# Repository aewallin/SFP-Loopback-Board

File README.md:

# SFP-Loopback-Board
SFP optical transciever loopback board. Connects SFP TX pins to RX pins, and provides buffered ( [ONET1191](http://www.ti.com/product/ONET1191P) )probe-outputs on SMA connectors.

See also [SFP+ timing calibration module](https://ohwr.org/project/wr-calibration/wikis/Electrical-absolute-calibration)

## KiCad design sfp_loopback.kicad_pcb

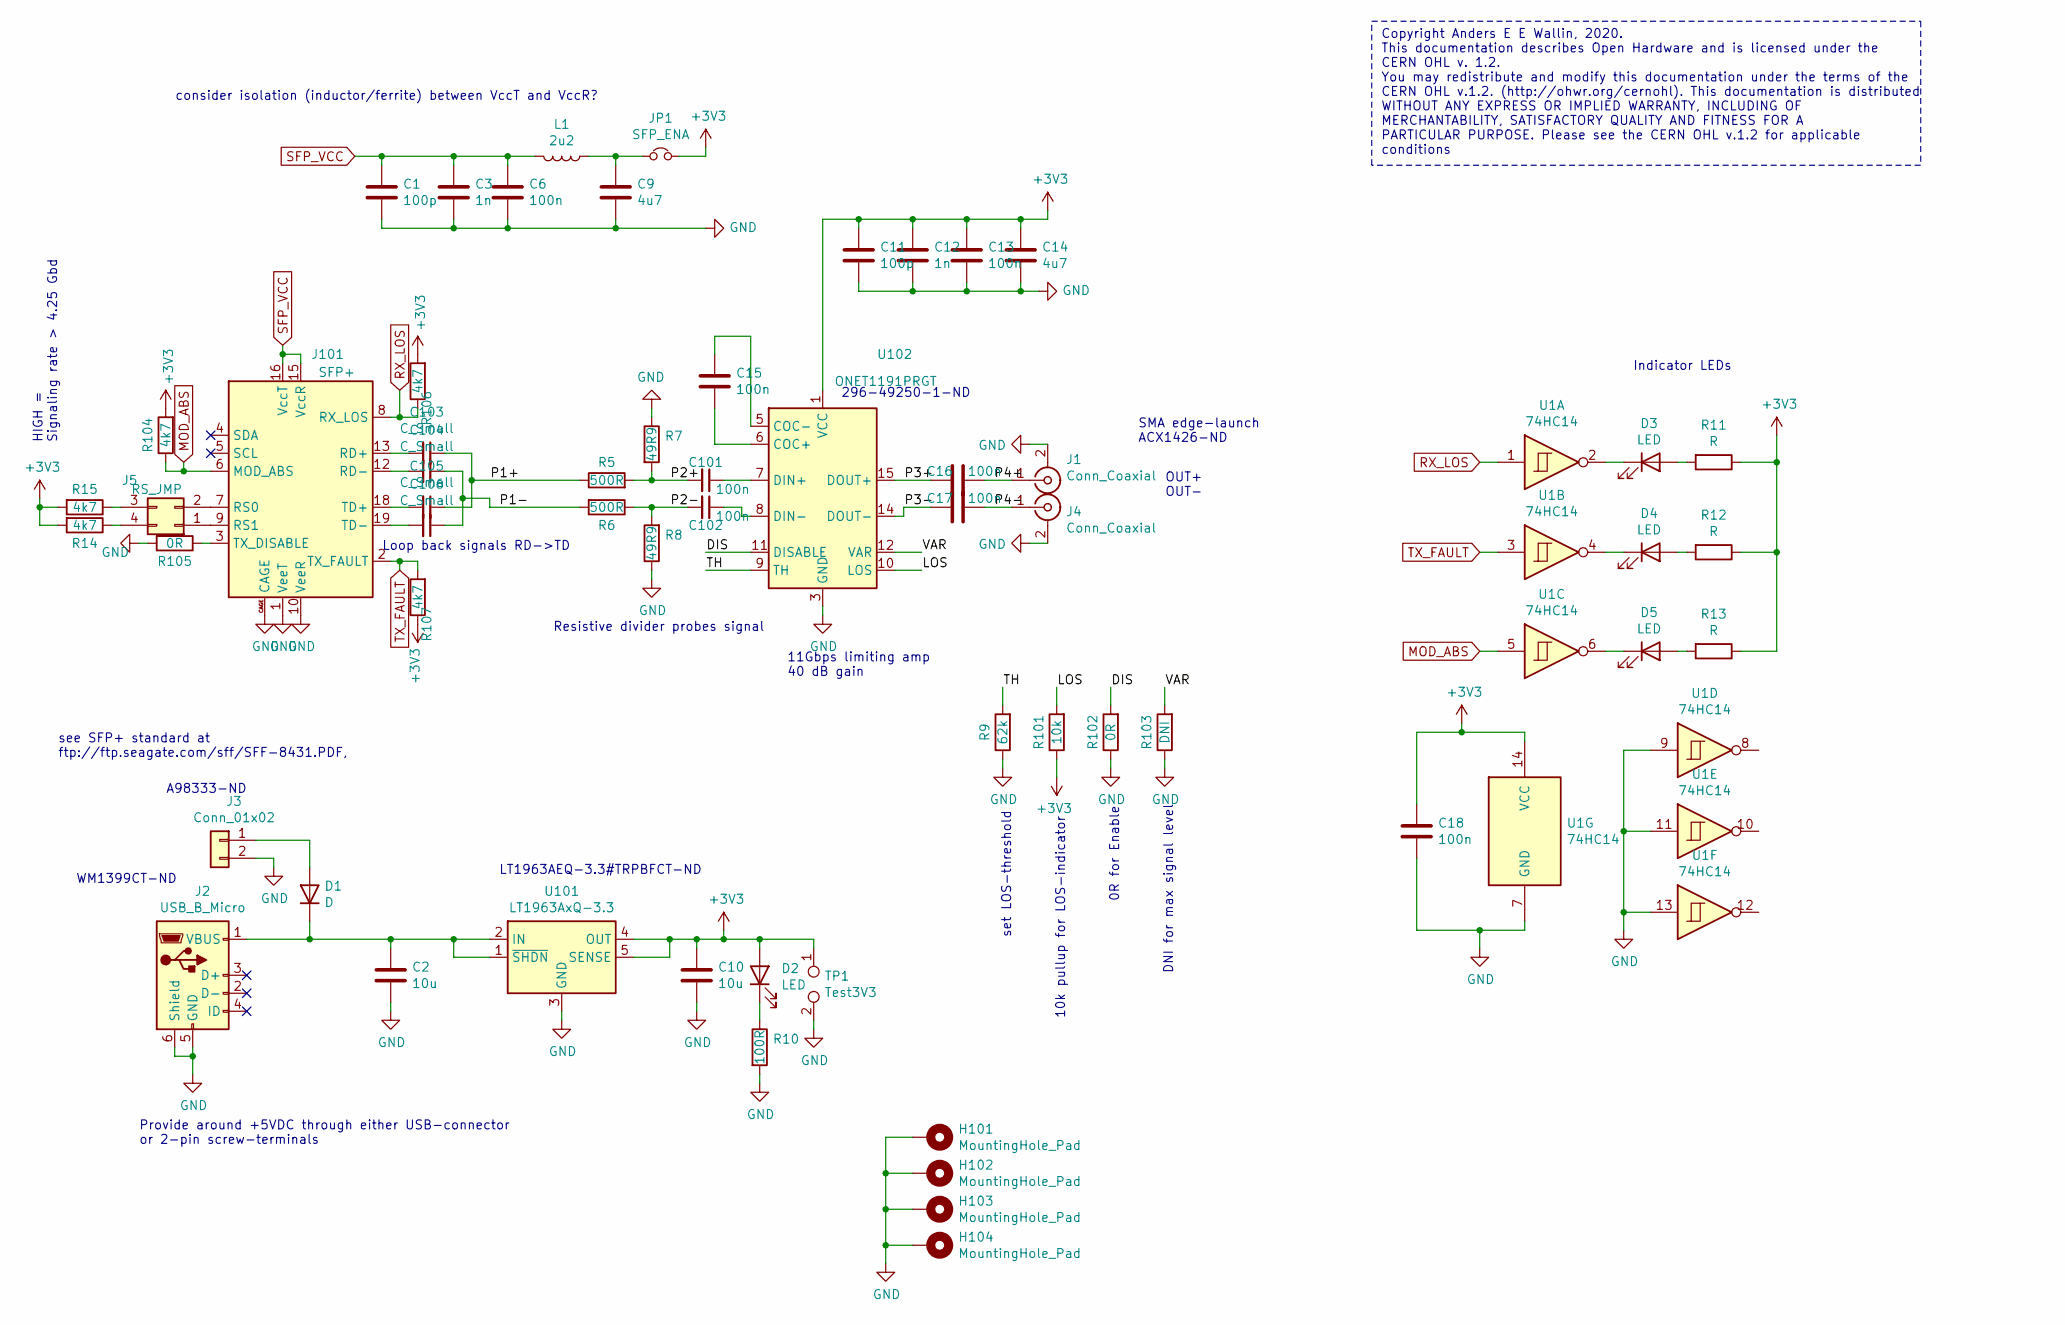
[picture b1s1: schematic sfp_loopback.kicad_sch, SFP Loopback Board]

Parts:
C1: 100p; C_0603
C2, C10: 10u; C_0805
C3, C12: 1n; C_0805
C6, C13, C16, C17, C18: 100n; C_0805
C9, C14: 4u7; C_0805
C11: 100p; C_0805
C15: 100n; C_0402
C101, C102: 100n; C_0402_1005Metric
C103, C104, C105, C106: C_Small; C_0402_1005Metric
D1: D; D_1206_3216Metric
D2, D3, D4, D5: LED; LED_0805
H101, H102, H103, H104: MountingHole_Pad; MountingHole_3.2mm_M3_DIN965_Pad
J1, J4: Conn_Coaxial; SMA_Amphenol_132289_EdgeMount
J2: USB_B_Micro; USB_Micro-B_Molex-105017-0001
J3: Conn_01x02; Pin_Header_Straight_1x02_Pitch2.54mm
J5: RS_JMP; Pin_Header_Straight_2x02_Pitch2.54mm
J101: SFP+; Connector_SFP_and_Cage
JP1: SFP_ENA; Pin_Header_Straight_1x02_Pitch2.54mm
L1: 2u2; L_0805
R5, R6: 500R; R_0402
R7, R8: 49R9; R_0402
R9: 62k; R_0805_2012Metric
R10: 100R; R_0805_2012Metric
R11, R12, R13: R; R_0805
R14, R15, R104, R106, R107: 4k7; R_0805_2012Metric
R101: 10k; R_0805_2012Metric
R102, R105: 0R; R_0805_2012Metric
R103: DNI; R_0805_2012Metric
TP1: Test3V3; Pin_Header_Straight_1x02_Pitch2.54mm
U1: 74HC14; TSSOP-14_4.4x5mm_Pitch0.65mm
U101: LT1963AxQ-3.3; TO-263-5_TabPin3
U102: ONET1191PRGT; VQFN-16-1EP_3x3mm_P0.5mm_EP1.68x1.68mm

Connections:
+3V3: C10.1, C11.2, C12.2, C13.2, C14.2, C18.1, D2.2 (A), JP1.2, R11.1, R12.1, R13.1, R14.2, R15.2, R101.1, R104.2, R106.2, R107.1, TP1.1, U1.14 (VCC), U101.4 (OUT), U101.5 (SENSE), U102.1 (VCC), U102.2 (VCC)
/DIS: R102.2, U102.11 (DISABLE)
/LOS: R101.2, U102.10 (LOS)
/P1+: C103.1, C105.1, R5.1
/P1-: C104.1, C106.1, R6.2
/P2+: C101.2, R5.2, R7.2
/P2-: C102.2, R6.1, R8.2
/P3+: C16.2, U102.15 (DOUT+)
/P3-: C17.2, U102.14 (DOUT-)
/P4+: C16.1, J1.1 (In)
/P4-: C17.1, J4.1 (In)
/TH: R9.2, U102.9 (TH)
/VAR: R103.2, U102.12 (VAR)
GND: C1.1, C2.2, C3.1, C6.1, C9.1, C10.2, C11.1, C12.1, C13.1, C14.1, C18.2, H101.1, H102.1, H103.1, H104.1, J1.2 (Ext), J2.5 (GND), J2.6 (Shield), J3.2, J4.2 (Ext), J101.1 (VeeT), J101.10 (VeeR), J101.11 (VeeR), J101.14 (VeeR), J101.17 (VeeT), J101.20 (VeeT), J101.CAGE, R7.1, R8.1, R9.1, R10.2, R102.1, R103.1, R105.2, TP1.2, U1.7 (GND), U1.9, U1.11, U1.13, U101.3 (GND), U102.3 (GND), U102.4 (GND), U102.13 (GND), U102.16 (GND), U102.17 (GND)
MOD_ABS: J101.6 (MOD_ABS), R104.1, U1.5
unnamed: C2.1, D1.1 (K), J2.1 (VBUS), U101.1 (~SHDN), U101.2 (IN)
unnamed: C9.2, JP1.1, L1.1
unnamed: C15.1, U102.6 (COC+)
unnamed: C15.2, U102.5 (COC-)
unnamed: C101.1, U102.7 (DIN+)
unnamed: C102.1, U102.8 (DIN-)
unnamed: C103.2, J101.13 (RD+)
unnamed: C104.2, J101.12 (RD-)
unnamed: C105.2, J101.18 (TD+)
unnamed: C106.2, J101.19 (TD-)
unnamed: D1.2 (A), J3.1
unnamed: D2.1 (K), R10.1
unnamed: D3.1 (K), U1.2
unnamed: D3.2 (A), R11.2
unnamed: D4.1 (K), U1.4
unnamed: D4.2 (A), R12.2
unnamed: D5.1 (K), U1.6
unnamed: D5.2 (A), R13.2
unnamed: J5.3, R15.1
unnamed: J5.4, R14.1
unnamed: J101.3 (TX_DISABLE), R105.1
unnamed: J5.2, J101.7 (RS0)
unnamed: J5.1, J101.9 (RS1)
RX_LOS: J101.8 (RX_LOS), R106.1, U1.1
SFP_VCC: C1.2, C3.2, C6.2, J101.15 (VccR), J101.16 (VccT), L1.2
TX_FAULT: J101.2 (TX_FAULT), R107.2, U1.3

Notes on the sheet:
Copyright Anders E E Wallin, 2020. This documentation describes Open Hardware and is licensed under the CERN OHL v. 1.2. You may redistribute and modify this documentation under the terms of the CERN OHL v.1.2. (http://ohwr.org/cernohl). This documentation is distributed WITHOUT ANY EXPRESS OR IMPL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
A98333-ND
SMA edge-launch ACX1426-ND
Resistive divider probes signal
HIGH = Signaling rate > 4.25 Gbd
10k pullup for LOS-indicator
OUT+ OUT-
WM1399CT-ND
11Gbps limiting amp 40 dB gain
Indicator LEDs
Loop back signals RD->TD
Provide around +5VDC through either USB-connector or 2-pin screw-terminals
0R for Enable
set LOS-threshold
LT1963AEQ-3.3#TRPBFCT-ND
DNI for max signal level
consider isolation (inductor/ferrite) between VccT and VccR?
see SFP+ standard at ftp://ftp.seagate.com/sff/SFF-8431.PDF,
296-49250-1-ND

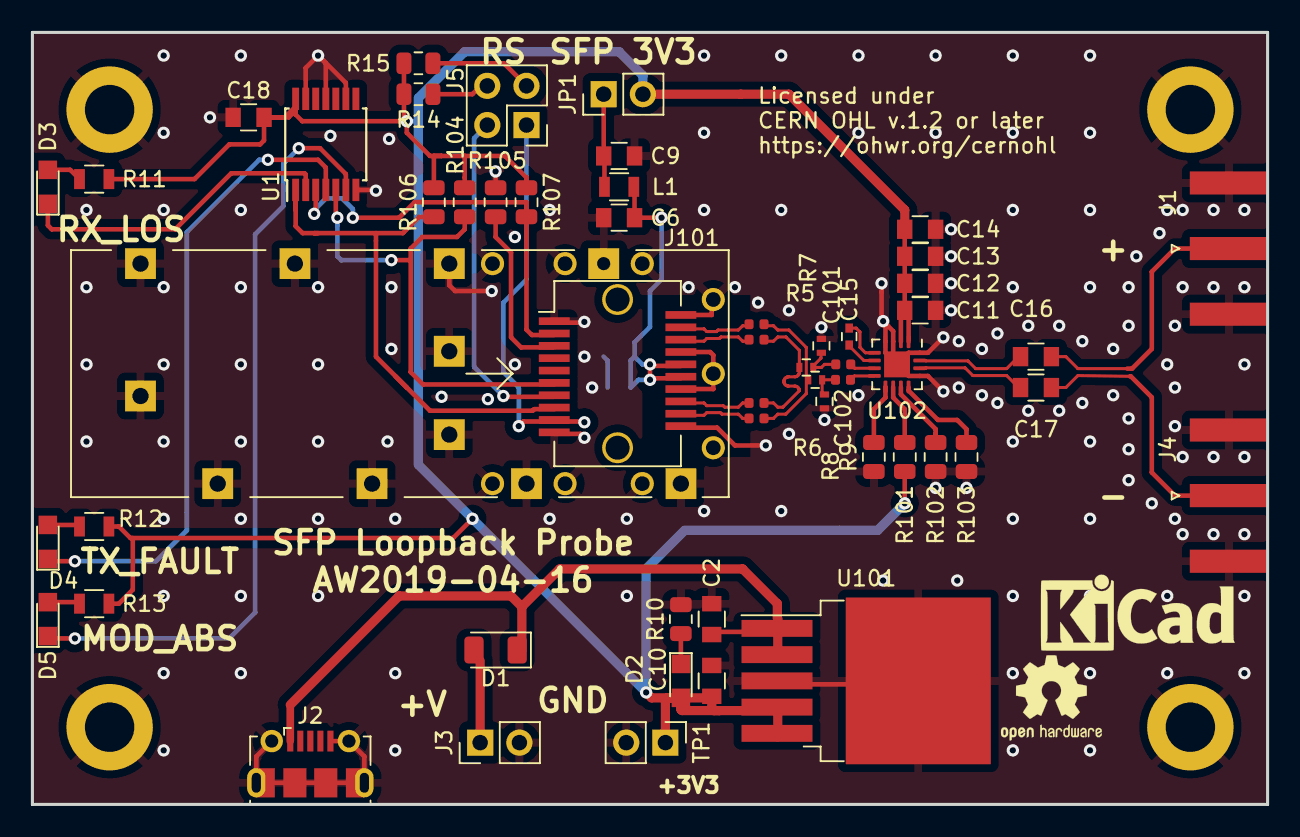
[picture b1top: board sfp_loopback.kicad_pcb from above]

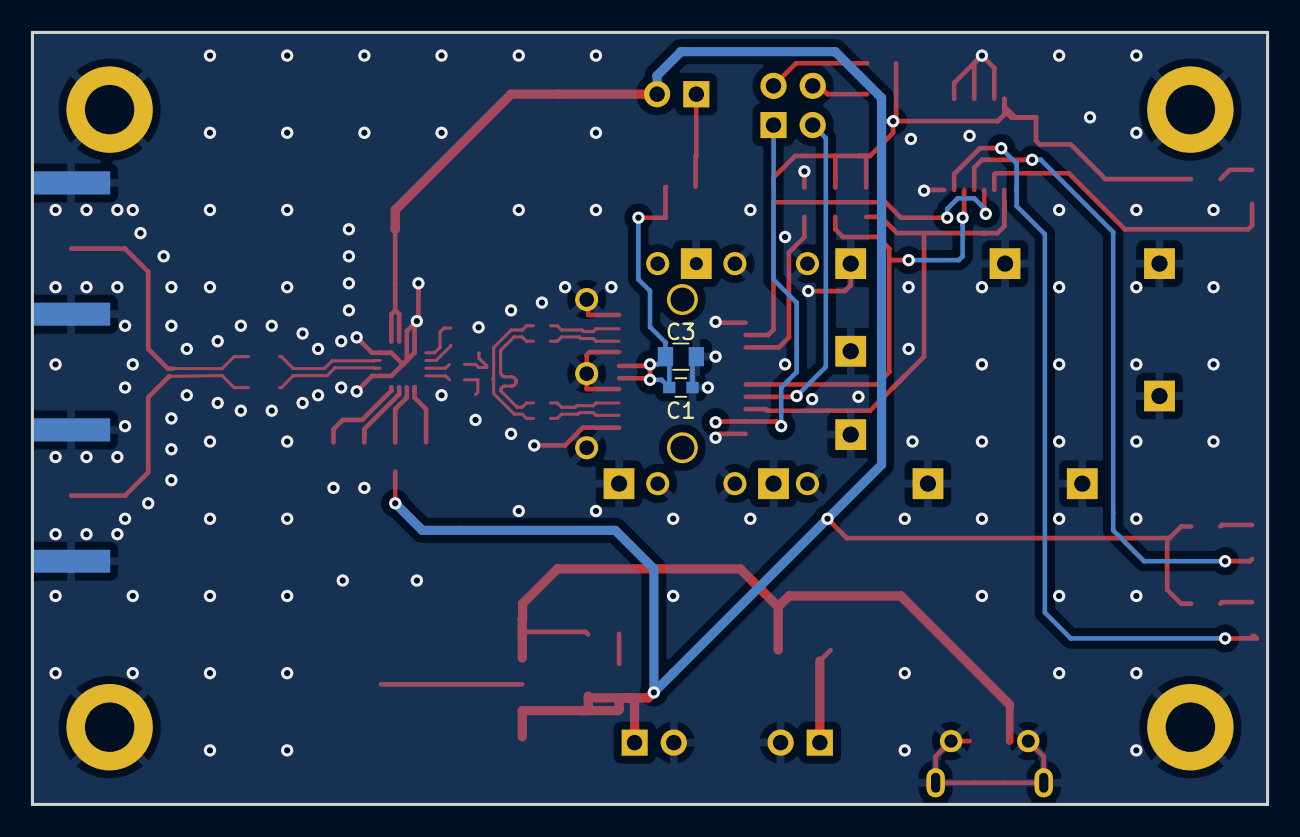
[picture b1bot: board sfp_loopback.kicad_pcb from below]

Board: 2 copper layers, 80.0 x 50.0 mm, 59 parts (2 on the bottom side), 41 nets.

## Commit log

2020-02-22 initial commit of files
2020-02-22 add PDFs
2020-02-22 text and image
2020-02-23 update pro file?
2025-11-29 update to kicad9

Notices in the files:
sfp_loopback.kicad_pcb:
CERN OHL v.1.2 or later
